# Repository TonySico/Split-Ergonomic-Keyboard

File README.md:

# Split-Ergonomic-Keyboard

All the files contained here are meant for public use and as a learning opportunity for those interested in creating their own custom AVR-based firmware from scratch without the use of libraries.

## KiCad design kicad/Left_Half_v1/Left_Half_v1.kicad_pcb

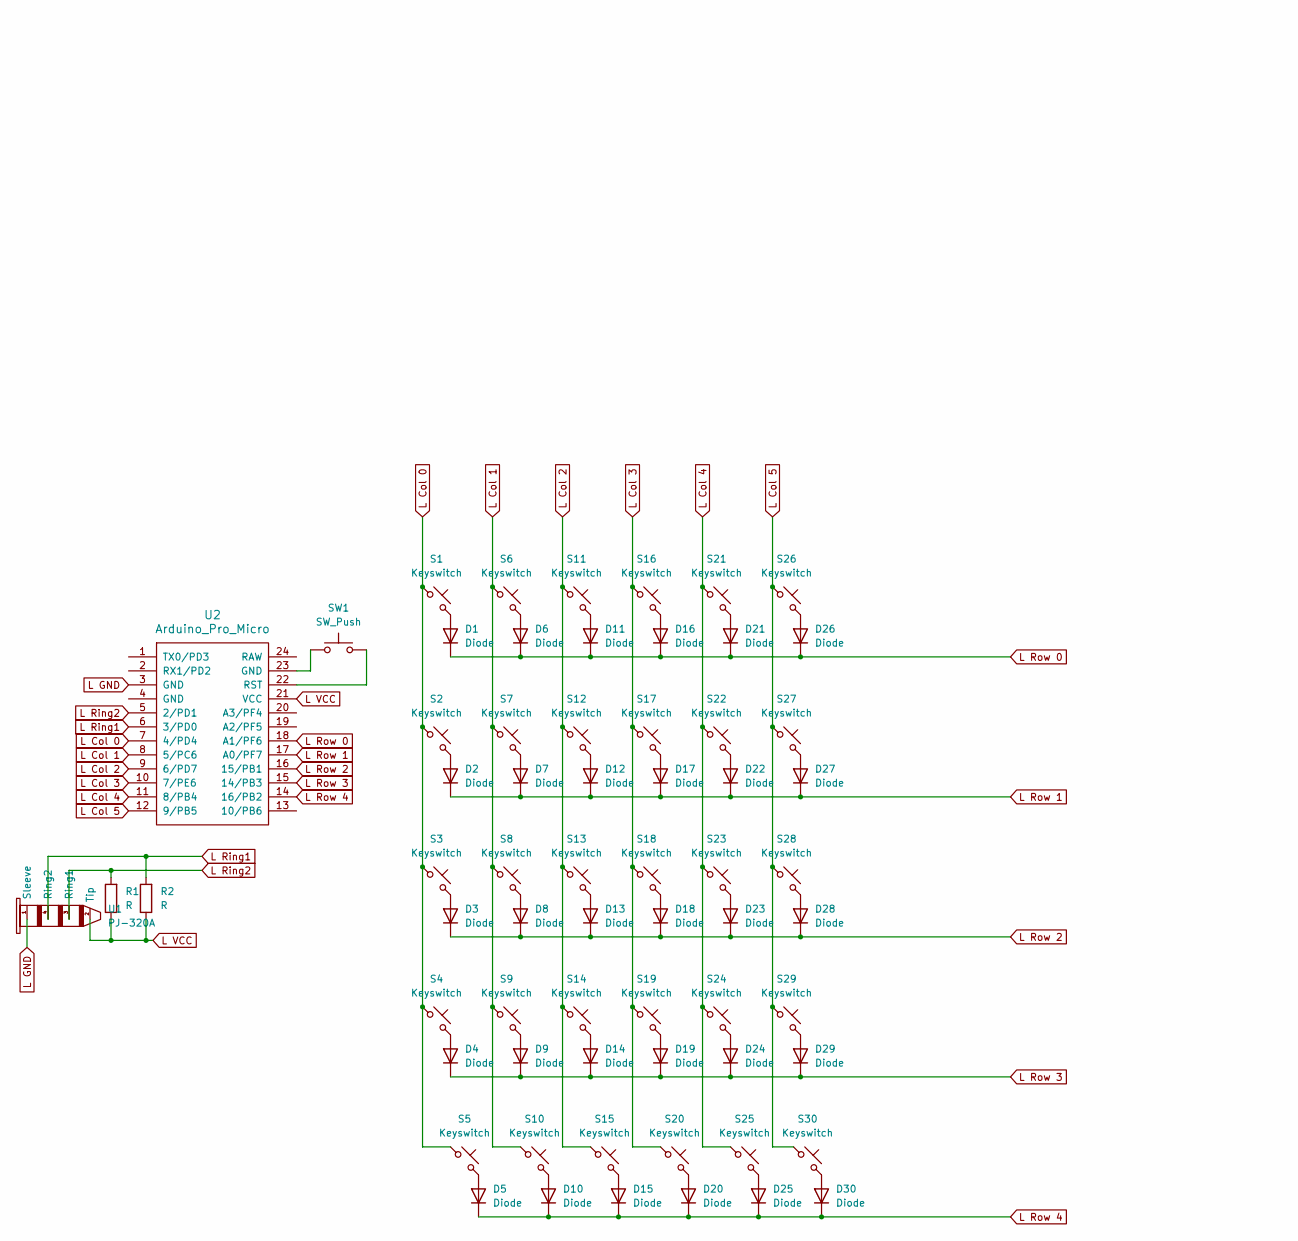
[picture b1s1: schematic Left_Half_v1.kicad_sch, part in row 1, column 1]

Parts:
D1, D2, D3, D4, D5, D6, D7, D8, D9, D10, D11, D12, D13, D14, D15, D16, D17, D18, D19, D20, D21, D22, D23, D24, D25, D26, D27, D28, D29, D30: Diode; D_DO-35_SOD27_P7.62mm_Horizontal
R1, R2: R; R_Axial_DIN0204_L3.6mm_D1.6mm_P5.08mm_Horizontal
S1, S2, S3, S4, S5, S6, S7, S8, S9, S10, S11, S12, S13, S14, S15, S16, S17, S18, S19, S20, S21, S22, S23, S24, S25, S26, S27, S28, S29, S30: Keyswitch; SW_choc_MxCombo_1u
SW1: SW_Push; SW_PUSH_6mm
U1: PJ-320A
U2: Arduino_Pro_Micro

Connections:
L Col 0: S1.1, S2.1, S3.1, S4.1, S5.1, U2.7 (4/PD4)
L Col 1: S6.1, S7.1, S8.1, S9.1, S10.1, U2.8 (5/PC6)
L Col 2: S11.1, S12.1, S13.1, S14.1, S15.1, U2.9 (6/PD7)
L Col 3: S16.1, S17.1, S18.1, S19.1, S20.1, U2.10 (7/PE6)
L Col 4: S21.1, S22.1, S23.1, S24.1, S25.1, U2.11 (8/PB4)
L Col 5: S26.1, S27.1, S28.1, S29.1, S30.1, U2.12 (9/PB5)
L GND: U1.1 (Sleeve), U2.3 (GND)
L Ring1: R2.2, U1.4 (Ring2), U2.6 (3/PD0)
L Ring2: R1.2, U1.3 (Ring1), U2.5 (2/PD1)
L Row 0: D1.1 (K), D6.1 (K), D11.1 (K), D16.1 (K), D21.1 (K), D26.1 (K), U2.18 (A1/PF6)
L Row 1: D2.1 (K), D7.1 (K), D12.1 (K), D17.1 (K), D22.1 (K), D27.1 (K), U2.17 (A0/PF7)
L Row 2: D3.1 (K), D8.1 (K), D13.1 (K), D18.1 (K), D23.1 (K), D28.1 (K), U2.16 (15/PB1)
L Row 3: D4.1 (K), D9.1 (K), D14.1 (K), D19.1 (K), D24.1 (K), D29.1 (K), U2.15 (14/PB3)
L Row 4: D5.1 (K), D10.1 (K), D15.1 (K), D20.1 (K), D25.1 (K), D30.1 (K), U2.14 (16/PB2)
L VCC: R1.1, R2.1, U1.2 (Tip), U2.21 (VCC)
unnamed: D1.2 (A), S1.2
unnamed: D2.2 (A), S2.2
unnamed: D3.2 (A), S3.2
unnamed: D4.2 (A), S4.2
unnamed: D5.2 (A), S5.2
unnamed: D6.2 (A), S6.2
unnamed: D7.2 (A), S7.2
unnamed: D8.2 (A), S8.2
unnamed: D9.2 (A), S9.2
unnamed: D10.2 (A), S10.2
unnamed: D11.2 (A), S11.2
unnamed: D12.2 (A), S12.2
unnamed: D13.2 (A), S13.2
unnamed: D14.2 (A), S14.2
unnamed: D15.2 (A), S15.2
unnamed: D16.2 (A), S16.2
unnamed: D17.2 (A), S17.2
unnamed: D18.2 (A), S18.2
unnamed: D19.2 (A), S19.2
unnamed: D20.2 (A), S20.2
unnamed: D21.2 (A), S21.2
unnamed: D22.2 (A), S22.2
unnamed: D23.2 (A), S23.2
unnamed: D24.2 (A), S24.2
unnamed: D25.2 (A), S25.2
unnamed: D26.2 (A), S26.2
unnamed: D27.2 (A), S27.2
unnamed: D28.2 (A), S28.2
unnamed: D29.2 (A), S29.2
unnamed: D30.2 (A), S30.2
unnamed: SW1.1, U2.23 (GND)
unnamed: SW1.2, U2.22 (RST)

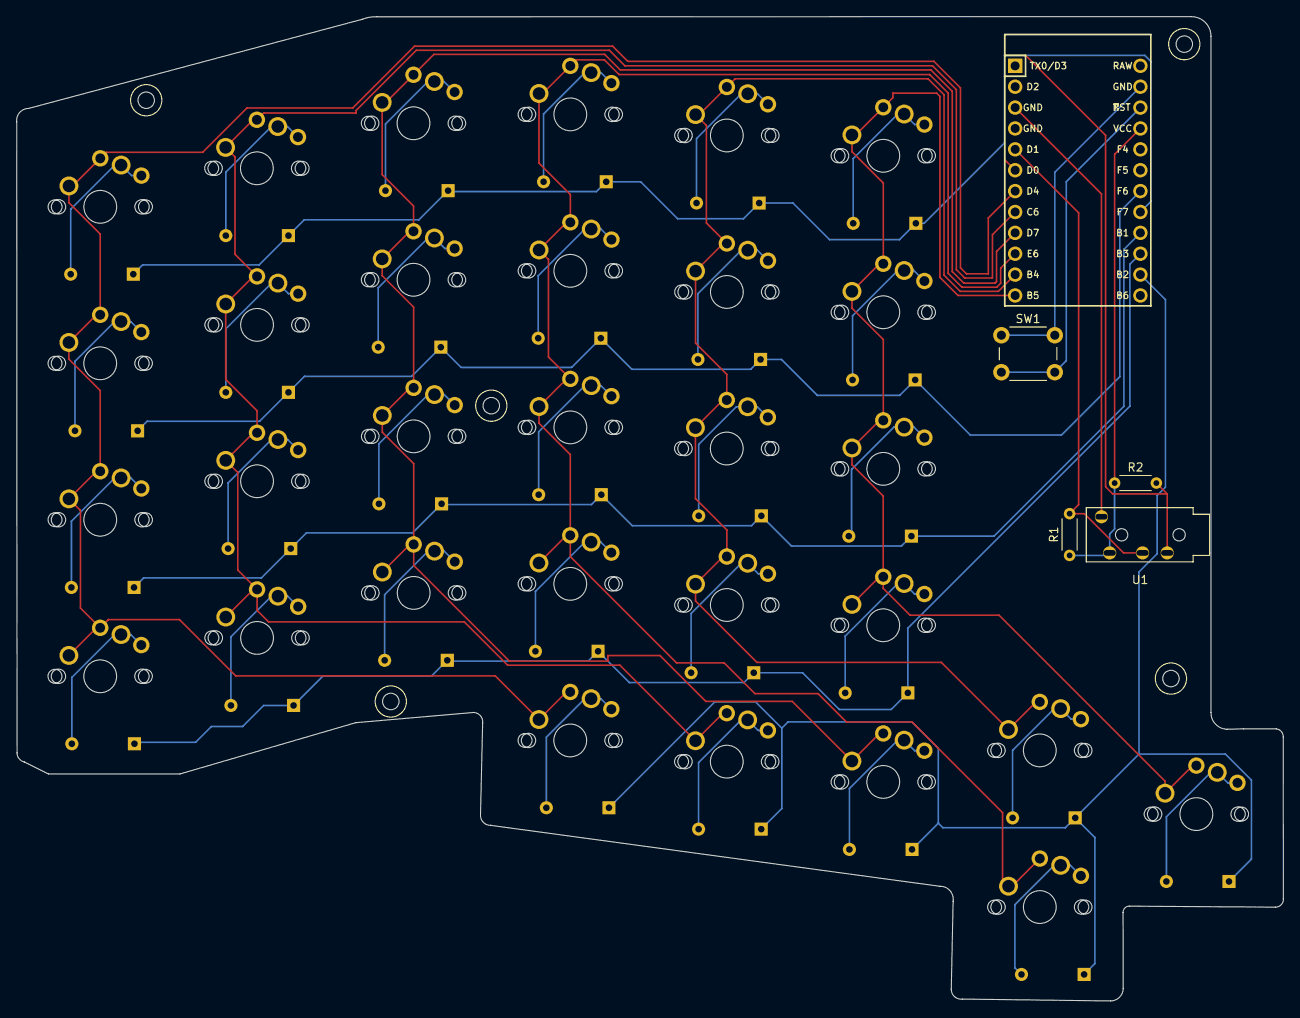
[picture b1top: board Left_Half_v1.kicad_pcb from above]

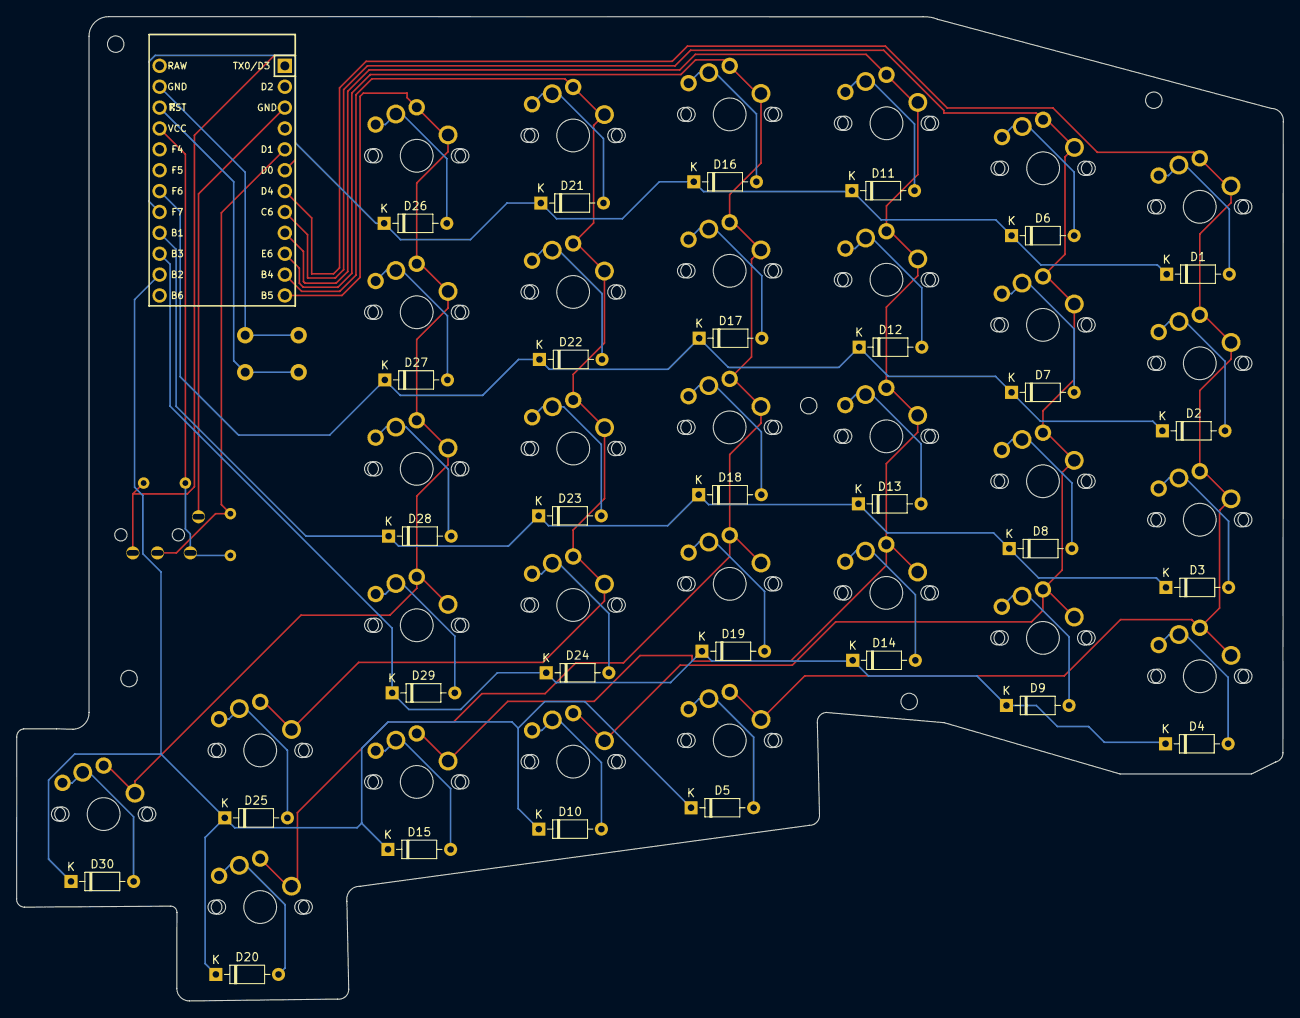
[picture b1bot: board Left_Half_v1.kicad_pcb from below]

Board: 2 copper layers, 154.1 x 119.8 mm, 65 parts (30 on the bottom side), 47 nets.

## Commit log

2025-06-17 [add] Source code
2025-06-17 [add] fix
2025-06-17 [add] ignore
2025-06-17 [add] remove PCB
2025-08-06 [add] working gui
2025-08-06 [add] progress debugging i2c stalls
2025-08-07 [fix] Working i2c on resets
2025-08-11 [add] start of layers and fix i2c
2025-08-14 [add] break to work later with layers
2025-08-25 [add] layers, almost
2025-09-02 [add] layers
2025-09-03 [add] uint16_t support
2025-09-04 [add] new mapping
2025-09-09 [add] blank support
2025-09-16 [add] new default layout
2025-09-24 [add] best mapping
